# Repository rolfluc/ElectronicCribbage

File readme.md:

Repo Housing everything related to the electronic cribbage board project.
SW/ Contains everything for SW, including for test boards.
EE/ Contains all electrical aspects
HW/ Contains all HW related aspects

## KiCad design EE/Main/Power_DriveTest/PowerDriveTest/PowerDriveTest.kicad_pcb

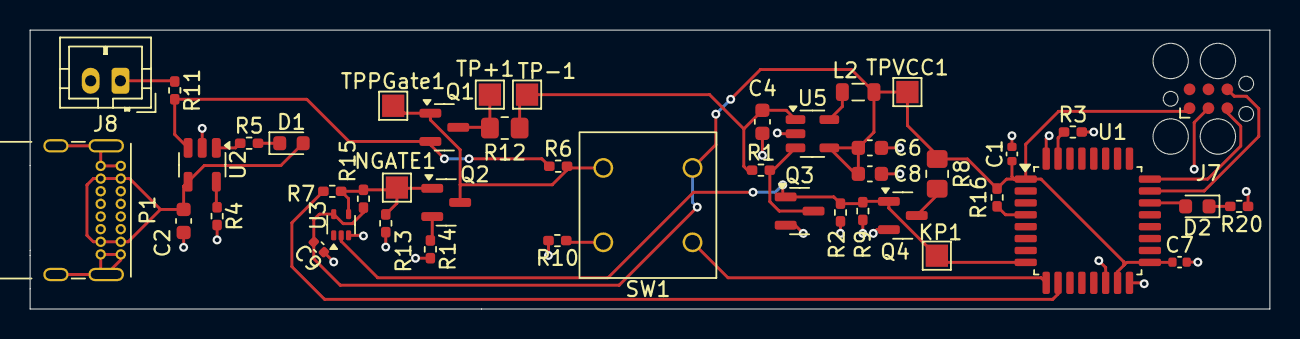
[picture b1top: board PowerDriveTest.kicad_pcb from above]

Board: 2 copper layers, 83.3 x 18.8 mm, 45 parts (0 on the bottom side), 26 nets.

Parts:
C1, C7, C9: 0.1u; C_0402_1005Metric
C2, C4, C6, C8: 4.7u; C_0603_1608Metric
D1, D2: LED; LED_0603_1608Metric
J7: TAG_CONNECT; Tag-Connect_TC2030-IDC-FP_2x03_P1.27mm_Vertical
J8: Conn_01x02_Male; JST_PH_B2B-PH-K_1x02_P2.00mm_Vertical
KP1: TestPoint; TestPoint_Pad_1.5x1.5mm
L2: 4.7u; L_0805_2012Metric
NGATE1: TestPoint; TestPoint_Pad_1.5x1.5mm
P1: USB_C_Plug_USB2.0; USB_C_Receptacle_GCT_USB4085
Q1: Q_PMOS_GSD; SOT-23
Q2, Q3, Q4: Q_NMOS_GSD; SOT-23
R1, R2, R9, R13: 100k; R_0402_1005Metric_Pad0.72x0.64mm_HandSolder
R3, R4, R10, R14, R16: 10k; R_0402_1005Metric_Pad0.72x0.64mm_HandSolder
R5, R20: 4.7k; R_0402_1005Metric_Pad0.72x0.64mm_HandSolder
R6: 1M; R_0402_1005Metric_Pad0.72x0.64mm_HandSolder
R7, R11: 0; R_0402_1005Metric_Pad0.72x0.64mm_HandSolder
R8: 10; R_0805_2012Metric_Pad1.20x1.40mm_HandSolder
R12: 25m; R_0805_2012Metric_Pad1.20x1.40mm_HandSolder
R15: 10K; R_0402_1005Metric_Pad0.72x0.64mm_HandSolder
SW1: SW_DPST; 401-1133-ND
TP+1: TestPoint; TestPoint_Pad_1.5x1.5mm
TP-1: TestPoint; TestPoint_Pad_1.5x1.5mm
TPPGate1: TestPoint; TestPoint_Pad_1.5x1.5mm
TPVCC1: TestPoint; TestPoint_Pad_1.5x1.5mm
U1: STM32G431K6Tx; LQFP-32_7x7mm_P0.8mm
U2: MCP73832-2-OT; SOT-23-5
U3: 74LVC1GU04DRL; SOT-553
U5: LM3670MF-3.3; TSOT-23-5

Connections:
+3V3: C1.1, C6.1, C7.1, C8.1, C9.1, J7.1 (POWER_3V3), L2.2, R8.1, R15.1, R16.1, SW1.1, TPVCC1.1, U1.1 (VDD), U1.15 (VDDA), U1.17 (VDD), U3.5 (VCC), U5.4 (FB)
/BTN_SNS: SW1.2, U1.9 (PA4)
/EN: Q3.3 (D), R1.2, U5.3 (EN)
/HB: D2.2 (A), U1.22 (PA12)
/KillPower: KP1.1, Q3.1 (G), Q4.1 (G), R2.1, R9.1, U1.8 (PA3), U3.2
/N_GATE: R7.1, U1.10 (PA5)
/N_SOURCE: Q2.2 (S), R14.1
/P_DRAIN: Q1.3 (D), R12.2, TP+1.1
/SWDCLK: J7.5 (SWCLK), U1.24 (PA14)
/SWDIO: J7.6 (SWDIO), U1.23 (PA13)
/VBAT: Q1.2 (S), R6.1, R11.2, U2.3 (VBAT)
/VBAT_OUT: C4.1, R1.1, R12.1, TP-1.1, U5.1 (Vin)
GND: C1.2, C2.2, C4.2, C6.2, C7.2, C8.2, C9.2, J7.3 (GND), J8.2, P1.A1 (GND), P1.A12 (GND), P1.B1 (GND), P1.B12 (GND), P1.S1 (SHIELD), Q3.2 (S), Q4.2 (S), R2.2, R3.2, R4.2, R9.2, R10.2, R13.2, R14.2, R20.1, U1.14 (VSSA), U1.16 (VSS), U1.32 (VSS), U2.2 (VSS), U3.3 (GND), U5.2 (GND)
unnamed: D1.1 (K), R5.2
unnamed: D2.1 (K), R20.2
unnamed: J8.1, R11.1
unnamed: Q1.1 (G), Q2.3 (D), R6.2, SW1.3, TPPGate1.1
unnamed: NGATE1.1, Q2.1 (G), R7.2, R13.1, R15.2, U3.4
unnamed: Q4.3 (D), R8.2
unnamed: R10.1, SW1.4
unnamed: R3.1, U1.31 (PB8)
unnamed: R16.2, U1.4 (PG10)
unnamed: R4.1, U2.5 (PROG)
unnamed: R5.1, U2.1 (STAT)
unnamed: L2.1, U5.5 (SW)
VBUS: C2.1, D1.2 (A), P1.A4 (VBUS), P1.A9 (VBUS), P1.B4 (VBUS), P1.B9 (VBUS), U2.4 (VDD)

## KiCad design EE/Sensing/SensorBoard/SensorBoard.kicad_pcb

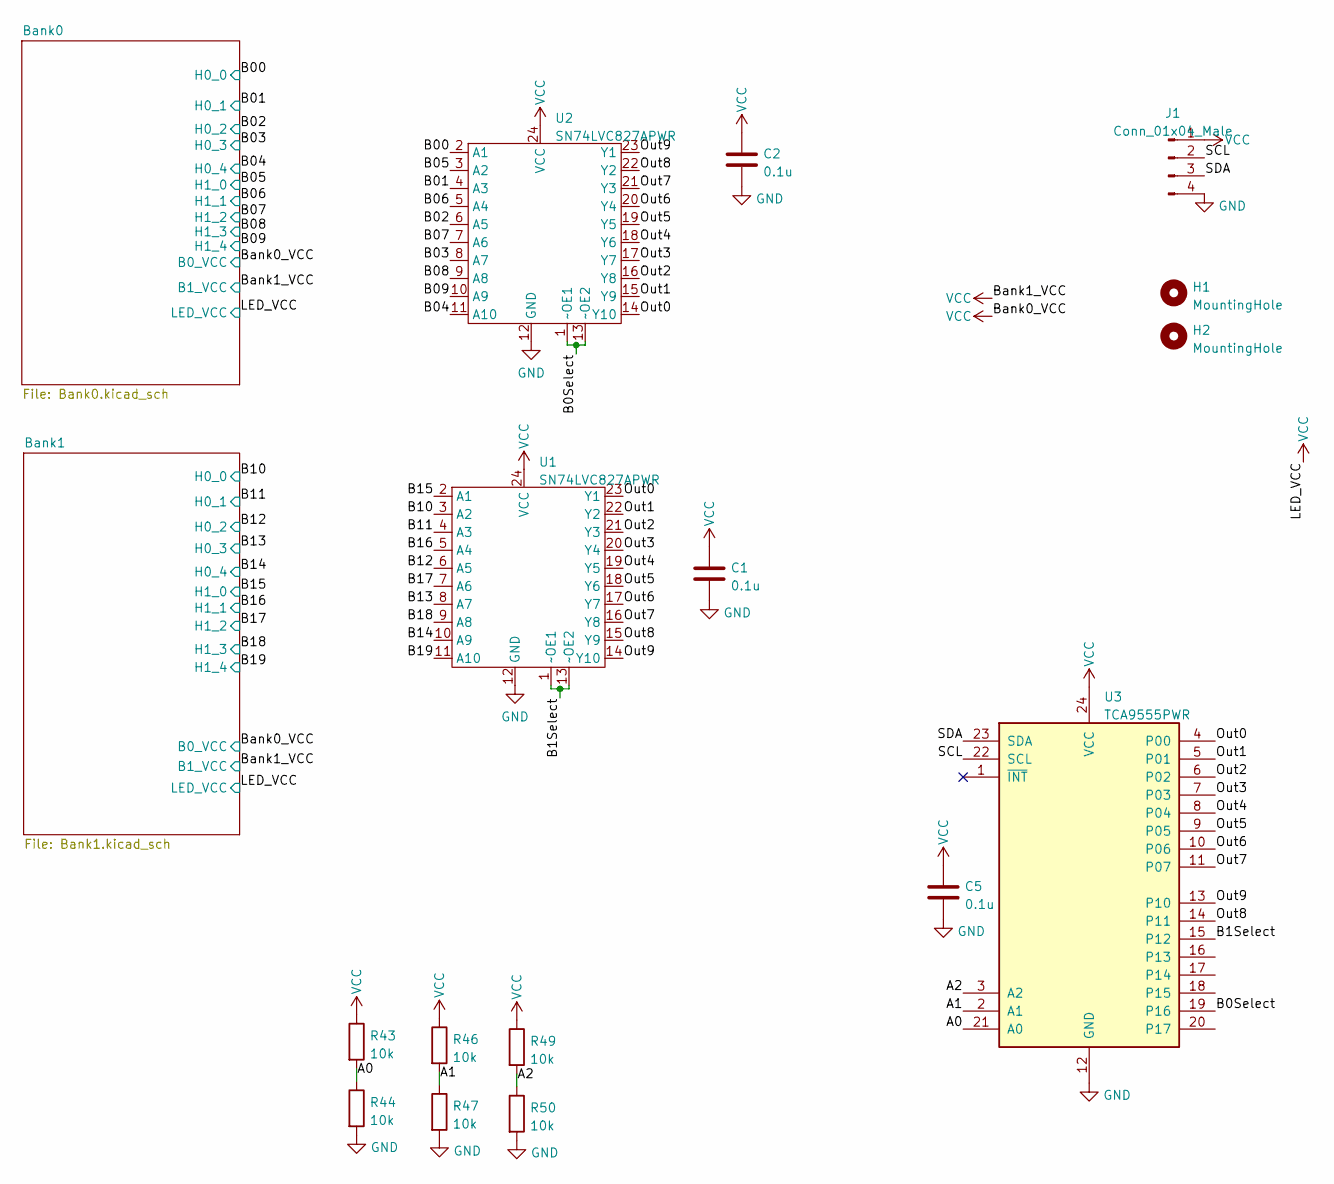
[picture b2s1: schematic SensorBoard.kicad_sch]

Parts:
C1, C2, C5: 0.1u; C_0402_1005Metric
H1, H2: MountingHole; MountingHole_2.5mm
J1: Conn_01x04_Male; PinSocket_1x04_P2.54mm_Vertical
R43, R44, R46, R47, R49, R50: 10k; R_0402_1005Metric
U1, U2: SN74LVC827APWR; TSSOP-24_4.4x7.8mm_P0.65mm
U3: TCA9555PWR; TSSOP-24_4.4x7.8mm_P0.65mm

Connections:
/A0: R43.2, R44.1, U3.21 (A0)
/A1: R46.2, R47.1, U3.2 (A1)
/A2: R49.2, R50.1, U3.3 (A2)
/B00: U2.2 (A1); also elsewhere on the board
/B0Select: U2.1 (~OE1), U2.13 (~OE2), U3.19 (P16)
/B01: U2.4 (A3); also elsewhere on the board
/B1Select: U1.1 (~OE1), U1.13 (~OE2), U3.15 (P12)
/B02: U2.6 (A5); also elsewhere on the board
/B03: U2.8 (A7); also elsewhere on the board
/B04: U2.11 (A10); also elsewhere on the board
/B05: U2.3 (A2); also elsewhere on the board
/B06: U2.5 (A4); also elsewhere on the board
/B07: U2.7 (A6); also elsewhere on the board
/B08: U2.9 (A8); also elsewhere on the board
/B09: U2.10 (A9); also elsewhere on the board
/B10: U1.3 (A2); also elsewhere on the board
/B11: U1.4 (A3); also elsewhere on the board
/B12: U1.6 (A5); also elsewhere on the board
/B13: U1.8 (A7); also elsewhere on the board
/B14: U1.10 (A9); also elsewhere on the board
/B15: U1.2 (A1); also elsewhere on the board
/B16: U1.5 (A4); also elsewhere on the board
/B17: U1.7 (A6); also elsewhere on the board
/B18: U1.9 (A8); also elsewhere on the board
/B19: U1.11 (A10); also elsewhere on the board
/Out0: U1.23 (Y1), U2.14 (Y10), U3.4 (P00)
/Out1: U1.22 (Y2), U2.15 (Y9), U3.5 (P01)
/Out2: U1.21 (Y3), U2.16 (Y8), U3.6 (P02)
/Out3: U1.20 (Y4), U2.17 (Y7), U3.7 (P03)
/Out4: U1.19 (Y5), U2.18 (Y6), U3.8 (P04)
/Out5: U1.18 (Y6), U2.19 (Y5), U3.9 (P05)
/Out6: U1.17 (Y7), U2.20 (Y4), U3.10 (P06)
/Out7: U1.16 (Y8), U2.21 (Y3), U3.11 (P07)
/Out8: U1.15 (Y9), U2.22 (Y2), U3.14 (P11)
/Out9: U1.14 (Y10), U2.23 (Y1), U3.13 (P10)
/SCL: J1.2, U3.22 (SCL)
/SDA: J1.3, U3.23 (SDA)
GND: C1.2, C2.2, C5.2, J1.4, R44.2, R47.2, R50.2, U1.12 (GND), U2.12 (GND), U3.12 (GND); also elsewhere on the board
VCC: C1.1, C2.1, C5.1, J1.1, R43.1, R46.1, R49.1, U1.24 (VCC), U2.24 (VCC), U3.24 (VCC); also elsewhere on the board

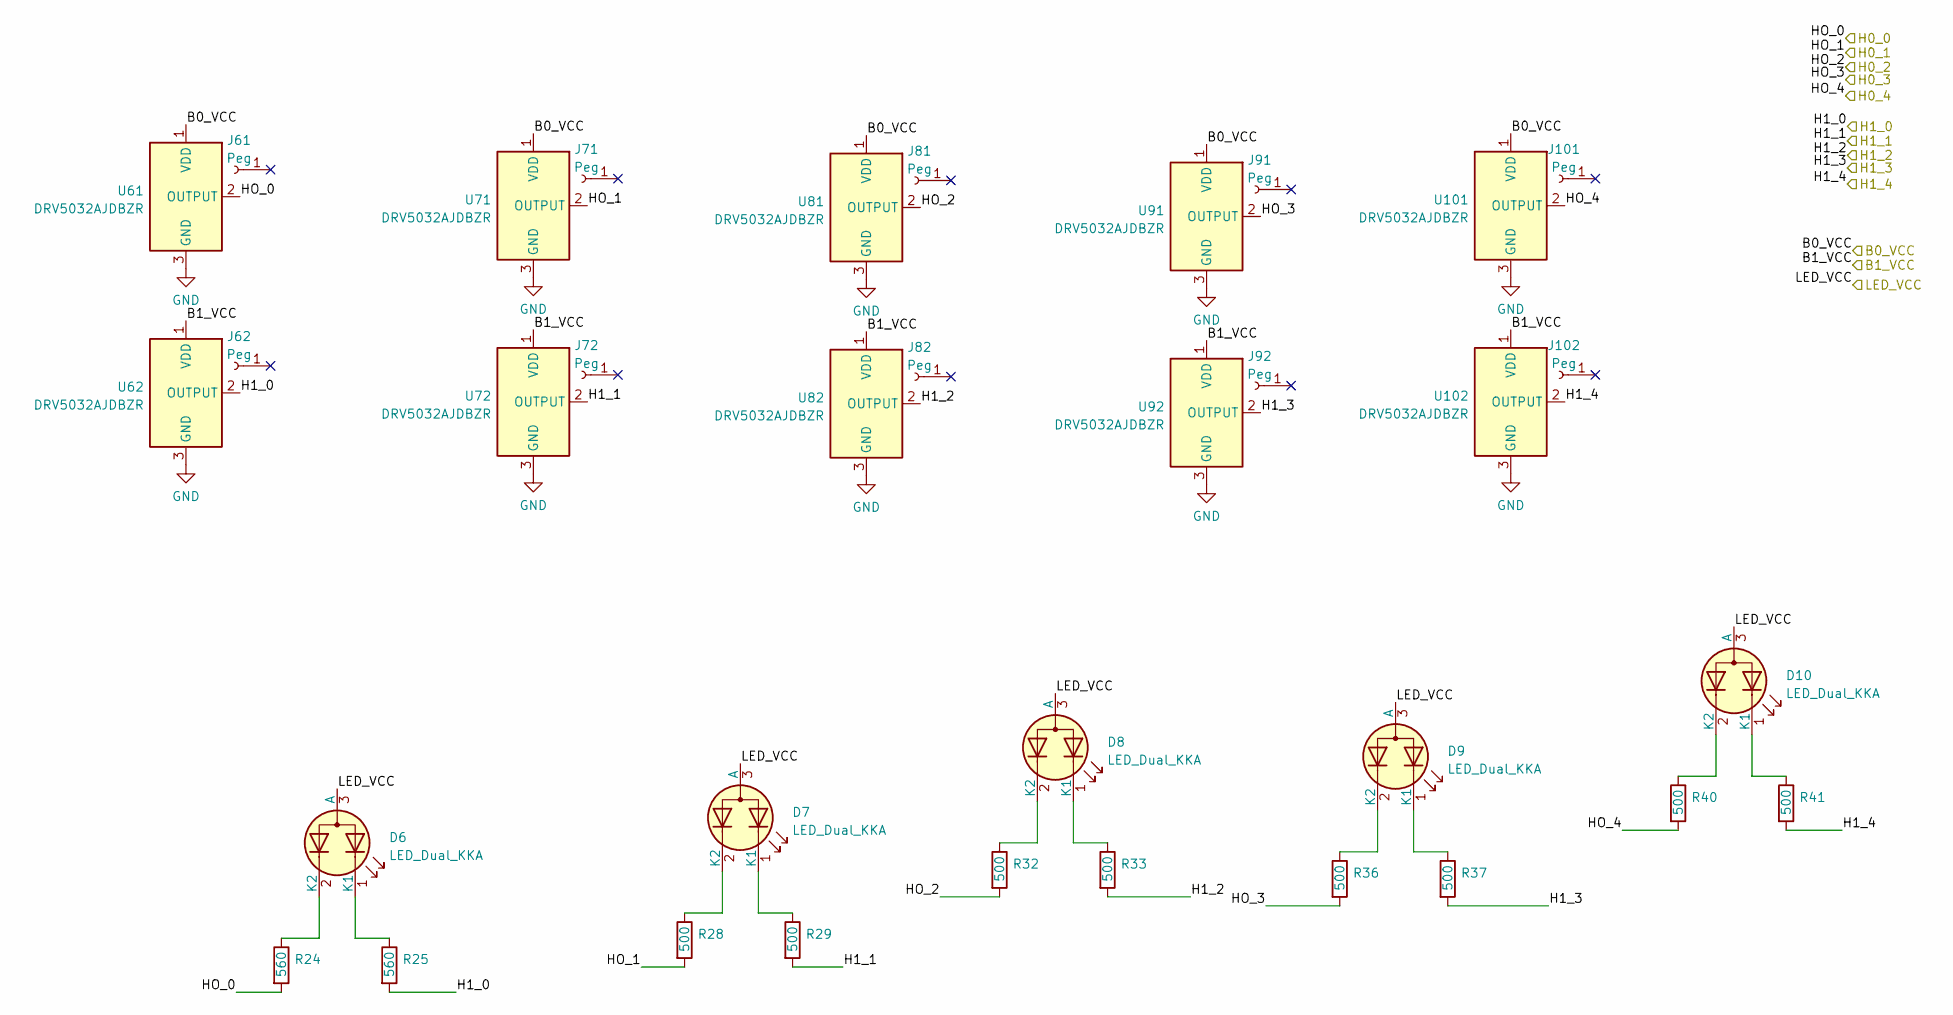
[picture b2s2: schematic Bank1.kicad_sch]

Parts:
D6, D7, D8, D9, D10: LED_Dual_KKA; SOT-23
J61, J62, J71, J72, J81, J82, J91, J92, J101, J102: Peg; TestPattern0
R24, R25: 560; R_0402_1005Metric_Pad0.72x0.64mm_HandSolder
R28, R29, R32, R33, R36, R37, R40, R41: 500; R_0402_1005Metric_Pad0.72x0.64mm_HandSolder
U61, U62, U71, U72, U81, U82, U91, U92, U101, U102: DRV5032AJDBZR; SOT-23

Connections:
/B10: R24.2, U61.2 (OUTPUT); also elsewhere on the board
/B11: R28.2, U71.2 (OUTPUT); also elsewhere on the board
/B12: R32.2, U81.2 (OUTPUT); also elsewhere on the board
/B13: R36.2, U91.2 (OUTPUT); also elsewhere on the board
/B14: R40.2, U101.2 (OUTPUT); also elsewhere on the board
/B15: R25.2, U62.2 (OUTPUT); also elsewhere on the board
/B16: R29.2, U72.2 (OUTPUT); also elsewhere on the board
/B17: R33.2, U82.2 (OUTPUT); also elsewhere on the board
/B18: R37.2, U92.2 (OUTPUT); also elsewhere on the board
/B19: R41.2, U102.2 (OUTPUT); also elsewhere on the board
GND: U61.3 (GND), U62.3 (GND), U71.3 (GND), U72.3 (GND), U81.3 (GND), U82.3 (GND), U91.3 (GND), U92.3 (GND), U101.3 (GND), U102.3 (GND); also elsewhere on the board
unnamed: D6.1 (K1), R25.1
unnamed: D6.2 (K2), R24.1
unnamed: D7.1 (K1), R29.1
unnamed: D7.2 (K2), R28.1
unnamed: D8.1 (K1), R33.1
unnamed: D8.2 (K2), R32.1
unnamed: D9.1 (K1), R37.1
unnamed: D9.2 (K2), R36.1
unnamed: D10.1 (K1), R41.1
unnamed: D10.2 (K2), R40.1
VCC: D6.3 (A), D7.3 (A), D8.3 (A), D9.3 (A), D10.3 (A), U61.1 (VDD), U62.1 (VDD), U71.1 (VDD), U72.1 (VDD), U81.1 (VDD), U82.1 (VDD), U91.1 (VDD), U92.1 (VDD), U101.1 (VDD), U102.1 (VDD); also elsewhere on the board

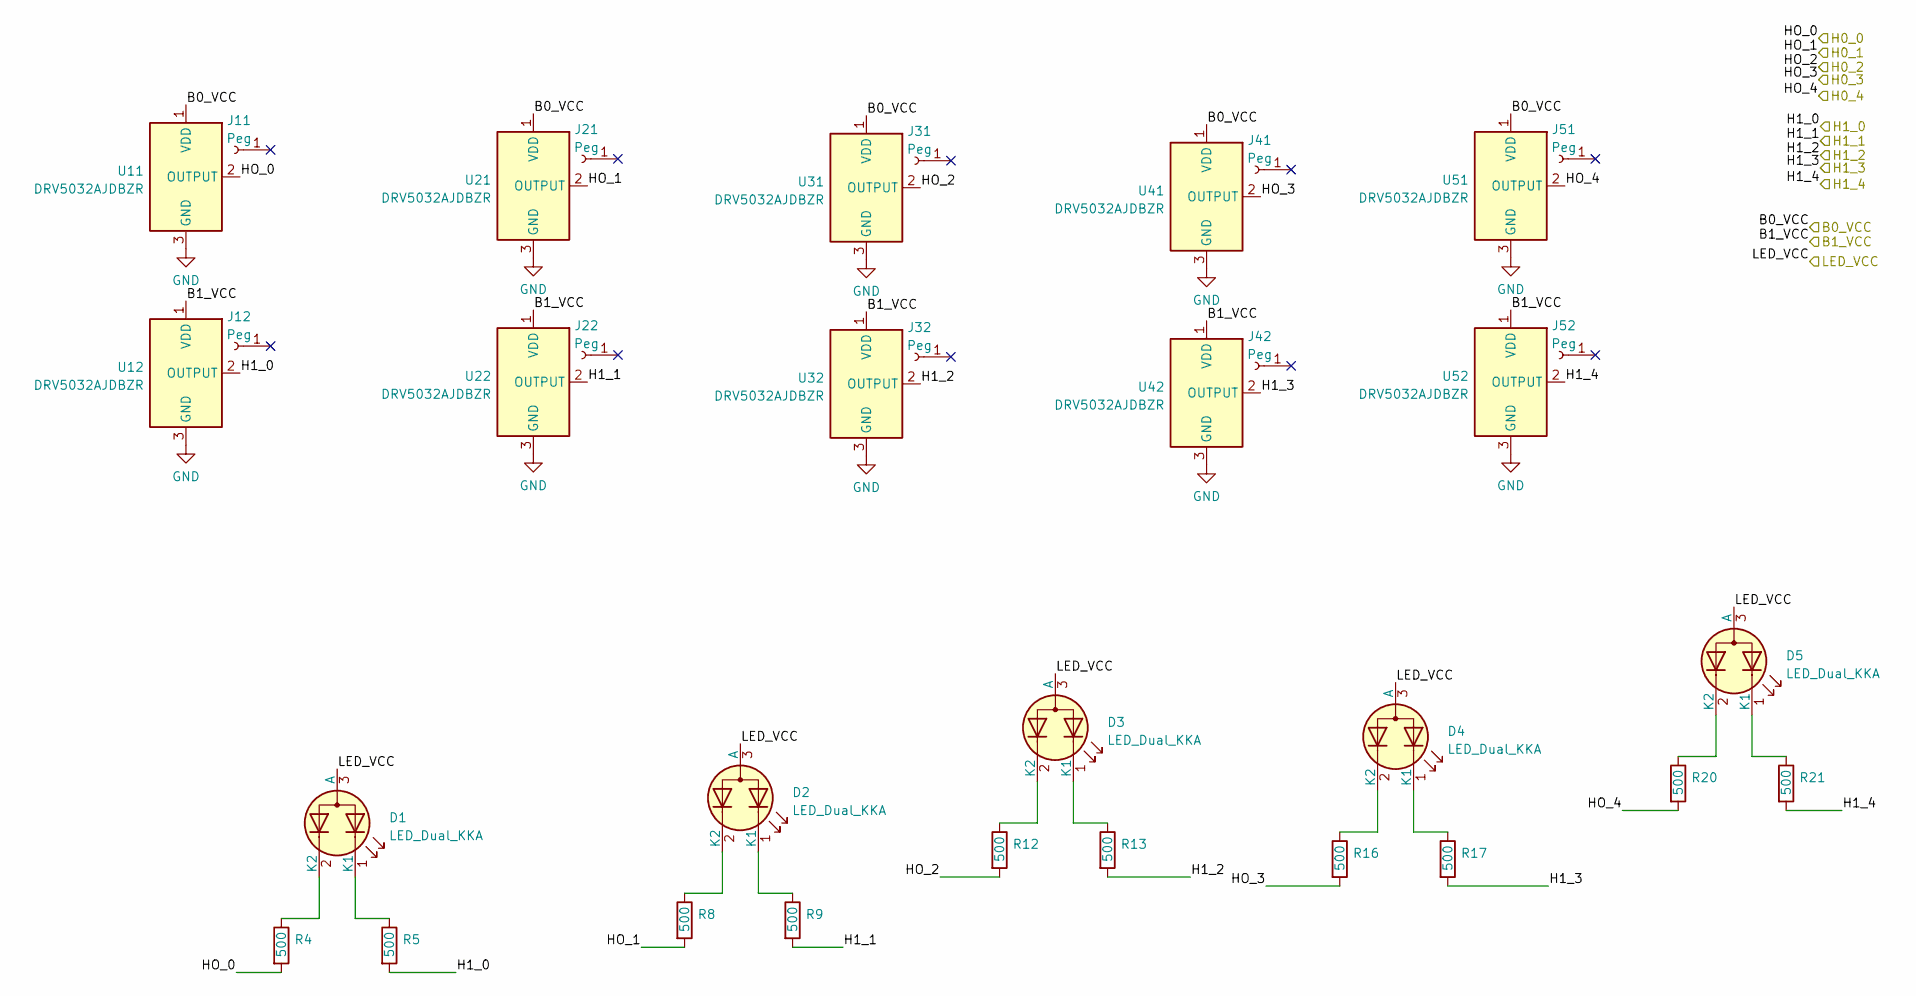
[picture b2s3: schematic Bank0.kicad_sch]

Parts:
D1, D2, D3, D4, D5: LED_Dual_KKA; SOT-23
J11, J12, J21, J22, J31, J32, J41, J42, J51, J52: Peg; TestPattern0
R4, R5, R8, R9, R12, R13, R16, R17, R20, R21: 500; R_0402_1005Metric_Pad0.72x0.64mm_HandSolder
U11, U12, U21, U22, U31, U32, U41, U42, U51, U52: DRV5032AJDBZR; SOT-23

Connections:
/B00: R4.2, U11.2 (OUTPUT); also elsewhere on the board
/B01: R8.2, U21.2 (OUTPUT); also elsewhere on the board
/B02: R12.2, U31.2 (OUTPUT); also elsewhere on the board
/B03: R16.2, U41.2 (OUTPUT); also elsewhere on the board
/B04: R20.2, U51.2 (OUTPUT); also elsewhere on the board
/B05: R5.2, U12.2 (OUTPUT); also elsewhere on the board
/B06: R9.2, U22.2 (OUTPUT); also elsewhere on the board
/B07: R13.2, U32.2 (OUTPUT); also elsewhere on the board
/B08: R17.2, U42.2 (OUTPUT); also elsewhere on the board
/B09: R21.2, U52.2 (OUTPUT); also elsewhere on the board
GND: U11.3 (GND), U12.3 (GND), U21.3 (GND), U22.3 (GND), U31.3 (GND), U32.3 (GND), U41.3 (GND), U42.3 (GND), U51.3 (GND), U52.3 (GND); also elsewhere on the board
unnamed: D1.1 (K1), R5.1
unnamed: D1.2 (K2), R4.1
unnamed: D2.1 (K1), R9.1
unnamed: D2.2 (K2), R8.1
unnamed: D3.1 (K1), R13.1
unnamed: D3.2 (K2), R12.1
unnamed: D4.1 (K1), R17.1
unnamed: D4.2 (K2), R16.1
unnamed: D5.1 (K1), R21.1
unnamed: D5.2 (K2), R20.1
VCC: D1.3 (A), D2.3 (A), D3.3 (A), D4.3 (A), D5.3 (A), U11.1 (VDD), U12.1 (VDD), U21.1 (VDD), U22.1 (VDD), U31.1 (VDD), U32.1 (VDD), U41.1 (VDD), U42.1 (VDD), U51.1 (VDD), U52.1 (VDD); also elsewhere on the board

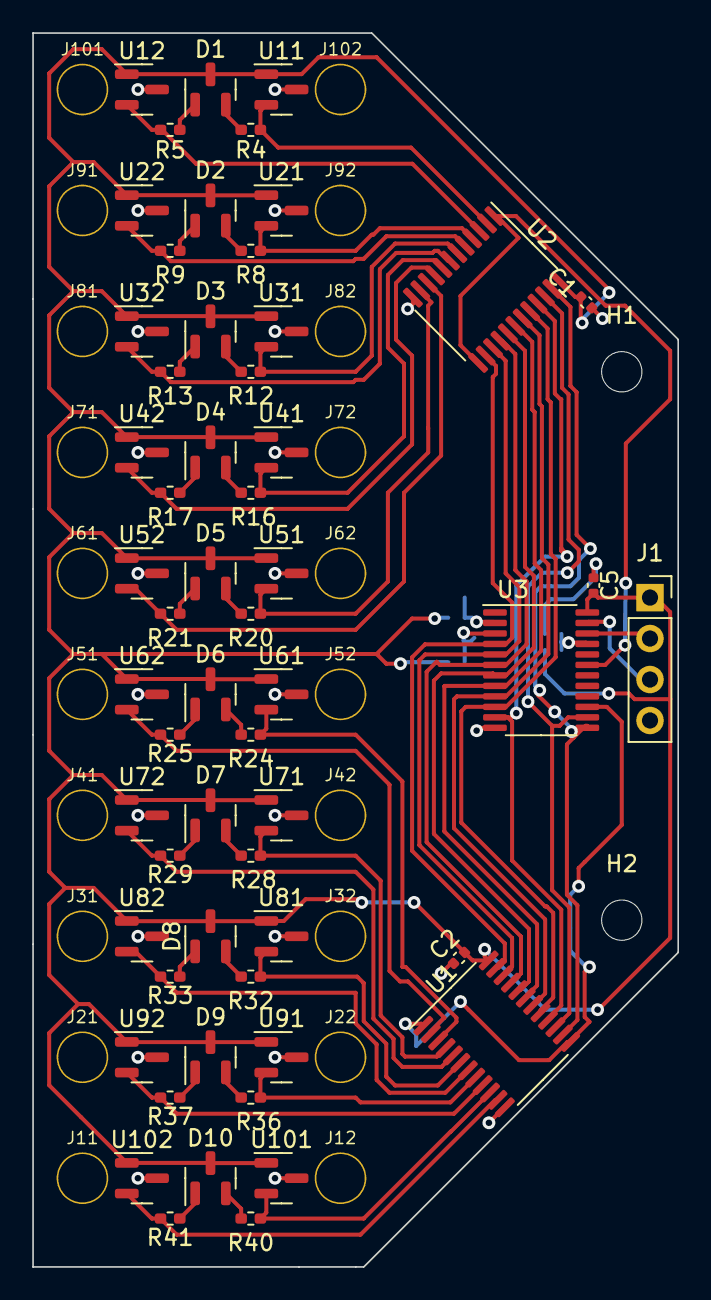
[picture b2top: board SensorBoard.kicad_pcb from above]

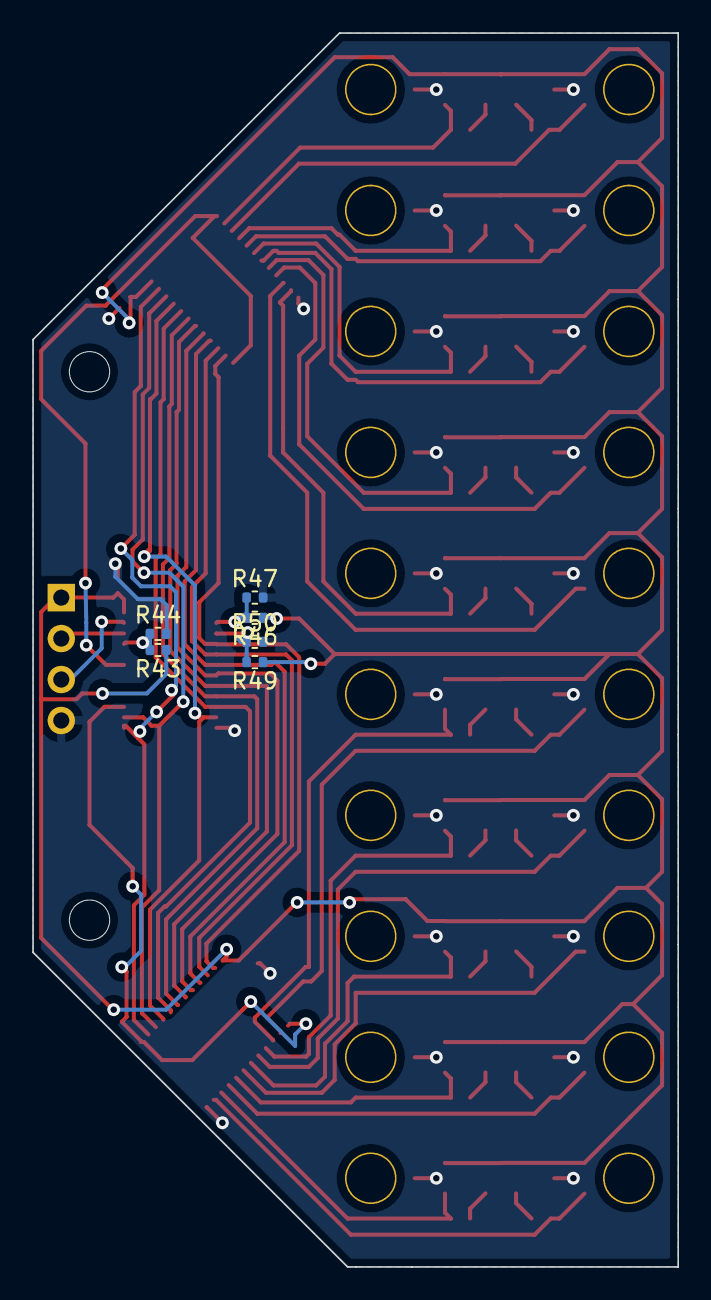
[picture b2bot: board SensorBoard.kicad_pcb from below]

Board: 2 copper layers, 40.0 x 76.5 mm, 85 parts (6 on the bottom side), 59 nets.

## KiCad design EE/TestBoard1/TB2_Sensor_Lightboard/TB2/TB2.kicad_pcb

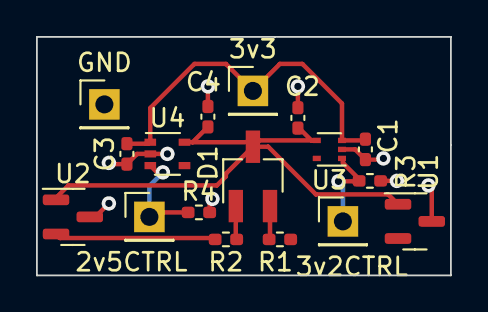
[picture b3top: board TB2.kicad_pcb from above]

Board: 2 copper layers, 23.0 x 13.2 mm, 17 parts (0 on the bottom side), 9 nets.

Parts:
2v5CTRL, 3v2CTRL, 3v3: Conn_01x01_Female; PinHeader_1x01_P2.54mm_Vertical
C1, C2, C3, C4: 0.1u; C_0402_1005Metric_Pad0.74x0.62mm_HandSolder
D1: LED_Dual_KKA; SC-59_Handsoldering
GND: Conn_01x01_Female; PinHeader_1x01_P2.54mm_Vertical
R1, R2: 1k; R_0402_1005Metric_Pad0.72x0.64mm_HandSolder
R3, R4: 100k; R_0402_1005Metric_Pad0.72x0.64mm_HandSolder
U1, U2: AH1381; SOT-23
U3: TCR2EE32; SOT-553
U4: MIC5365-2.5YC5; SOT-353_SC-70-5

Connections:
+3V3: 3v3.1, C1.1, C3.1, U3.3 (VIN), U4.1 (VIN)
/2v5_CTRL: 2v5CTRL.1, R4.1, U4.3 (EN)
/3v2_CTRL: 3v2CTRL.1, R3.1, U3.1 (CTRL)
/HO_0: R1.2, U1.2 (OUTPUT)
/HO_1: R2.2, U2.2 (OUTPUT)
GND: C1.2, C2.2, C3.2, C4.2, GND.1, R3.2, R4.2, U1.3 (GND), U2.3 (GND), U3.2 (GND), U4.2 (GND)
unnamed: D1.1 (K1), R2.1
unnamed: D1.2 (K2), R1.1
VCC: C2.1, C4.1, D1.3 (A), U1.1 (VDD), U2.1 (VDD), U3.4 (VOUT), U4.5 (VOUT)

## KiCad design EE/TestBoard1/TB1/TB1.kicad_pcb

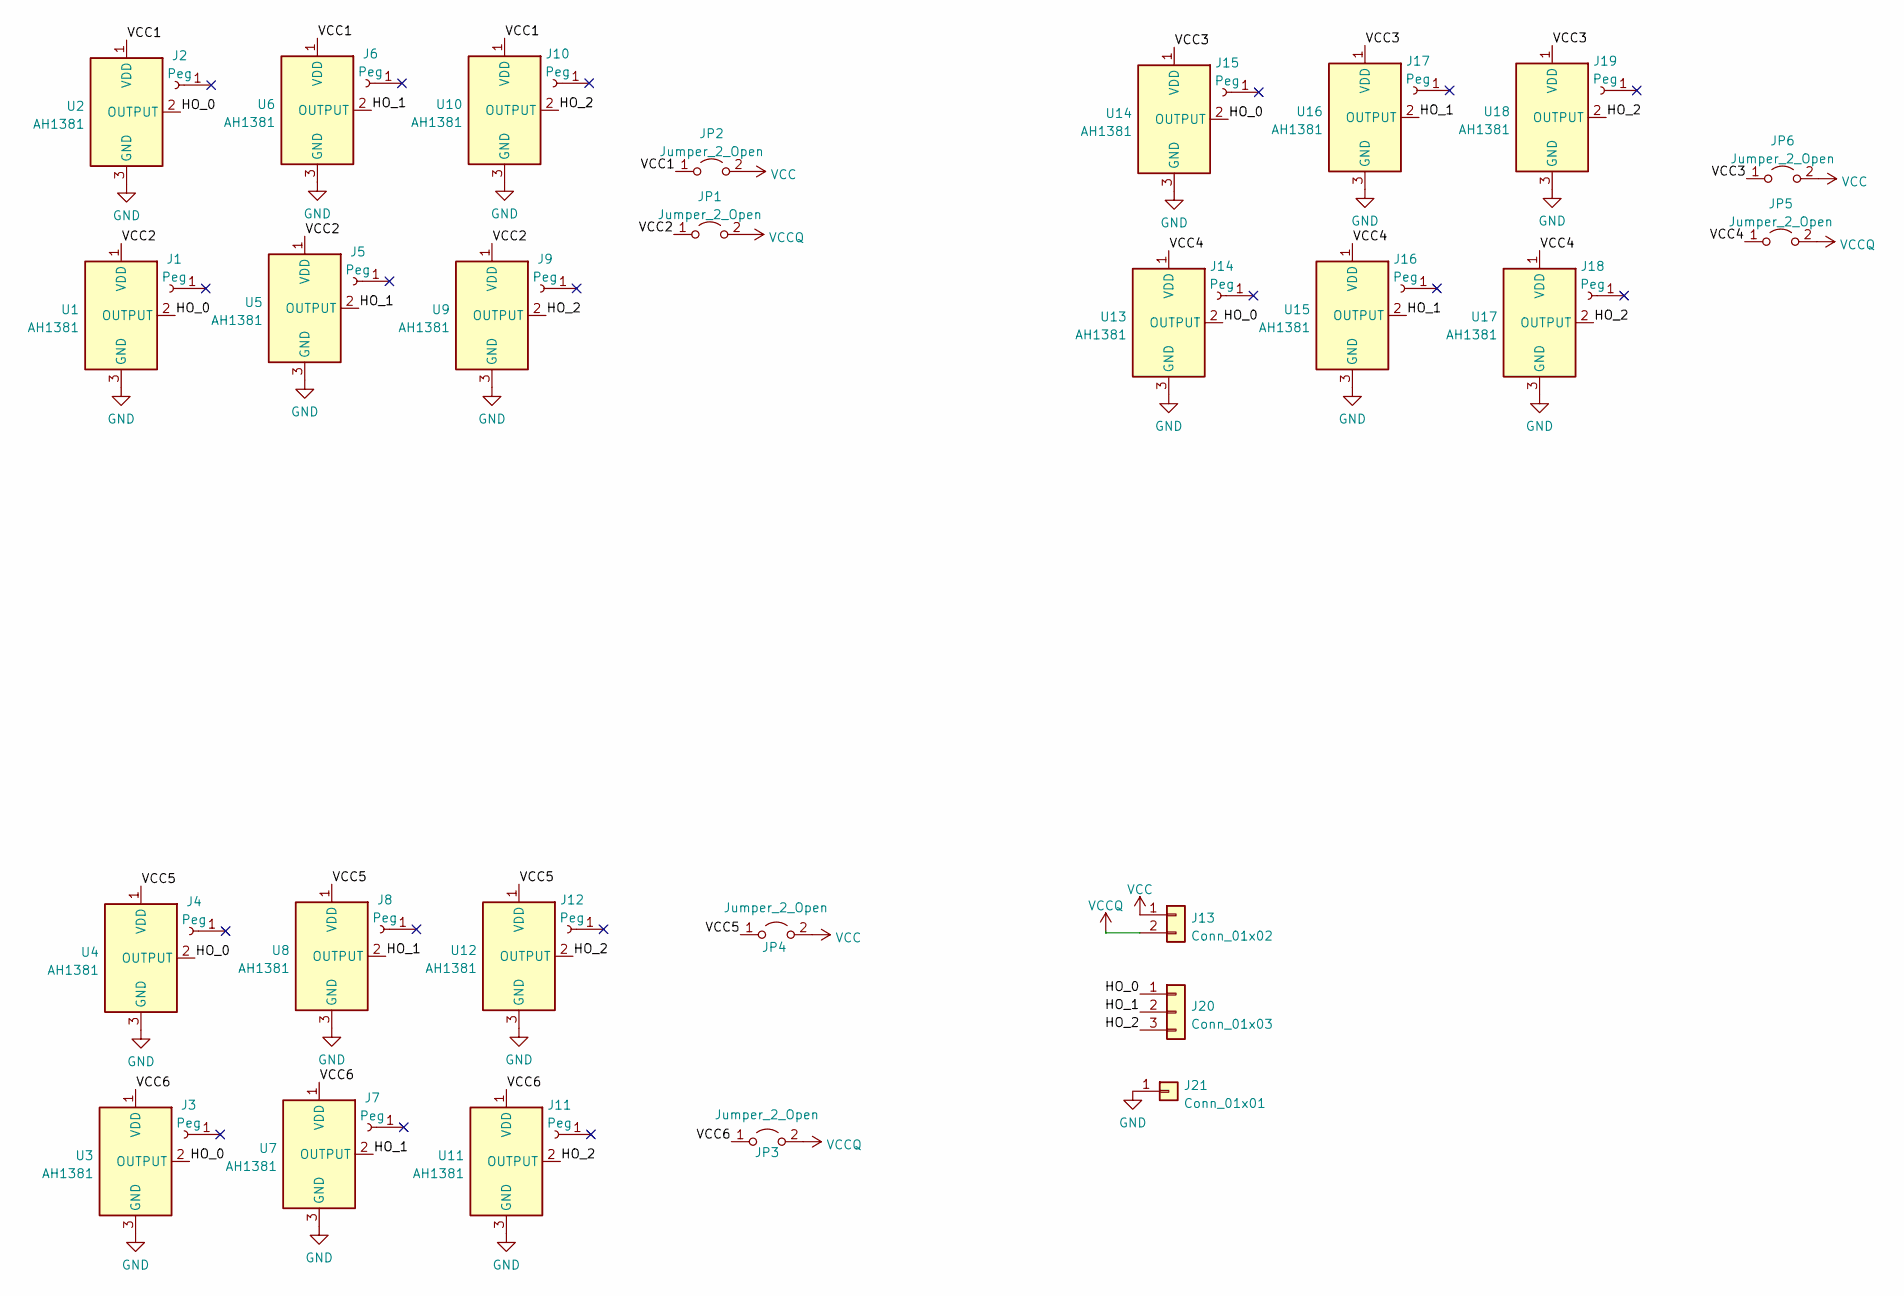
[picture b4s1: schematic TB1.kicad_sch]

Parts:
J1, J2, J5, J6, J9, J10: Peg; TestPattern0
J3, J4, J7, J8, J11, J12: Peg; TestPattern1
J13: Conn_01x02; PinHeader_1x02_P2.54mm_Vertical
J14, J15, J16, J17, J18, J19: Peg; TestPattern2
J20: Conn_01x03; PinHeader_1x03_P2.54mm_Vertical
J21: Conn_01x01; PinHeader_1x01_P2.54mm_Vertical
JP1, JP2, JP3, JP4, JP5, JP6: Jumper_2_Open; SolderJumper-2_P1.3mm_Open_Pad1.0x1.5mm
U1, U2, U3, U4, U5, U6, U7, U8, U9, U10, U11, U12, U13, U14, U15, U16, U17, U18: AH1381; SOT-23

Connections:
/HO_0: J20.1, U1.2 (OUTPUT), U2.2 (OUTPUT), U3.2 (OUTPUT), U4.2 (OUTPUT), U13.2 (OUTPUT), U14.2 (OUTPUT)
/HO_1: J20.2, U5.2 (OUTPUT), U6.2 (OUTPUT), U7.2 (OUTPUT), U8.2 (OUTPUT), U15.2 (OUTPUT), U16.2 (OUTPUT)
/HO_2: J20.3, U9.2 (OUTPUT), U10.2 (OUTPUT), U11.2 (OUTPUT), U12.2 (OUTPUT), U17.2 (OUTPUT), U18.2 (OUTPUT)
/VCC1: JP2.1 (A), U2.1 (VDD), U6.1 (VDD), U10.1 (VDD)
/VCC2: JP1.1 (A), U1.1 (VDD), U5.1 (VDD), U9.1 (VDD)
/VCC3: JP6.1 (A), U14.1 (VDD), U16.1 (VDD), U18.1 (VDD)
/VCC4: JP5.1 (A), U13.1 (VDD), U15.1 (VDD), U17.1 (VDD)
/VCC5: JP4.1 (A), U4.1 (VDD), U8.1 (VDD), U12.1 (VDD)
/VCC6: JP3.1 (A), U3.1 (VDD), U7.1 (VDD), U11.1 (VDD)
GND: J21.1, U1.3 (GND), U2.3 (GND), U3.3 (GND), U4.3 (GND), U5.3 (GND), U6.3 (GND), U7.3 (GND), U8.3 (GND), U9.3 (GND), U10.3 (GND), U11.3 (GND), U12.3 (GND), U13.3 (GND), U14.3 (GND), U15.3 (GND), U16.3 (GND), U17.3 (GND), U18.3 (GND)
VCC: J13.1, JP2.2 (B), JP4.2 (B), JP6.2 (B)
VCCQ: J13.2, JP1.2 (B), JP3.2 (B), JP5.2 (B)

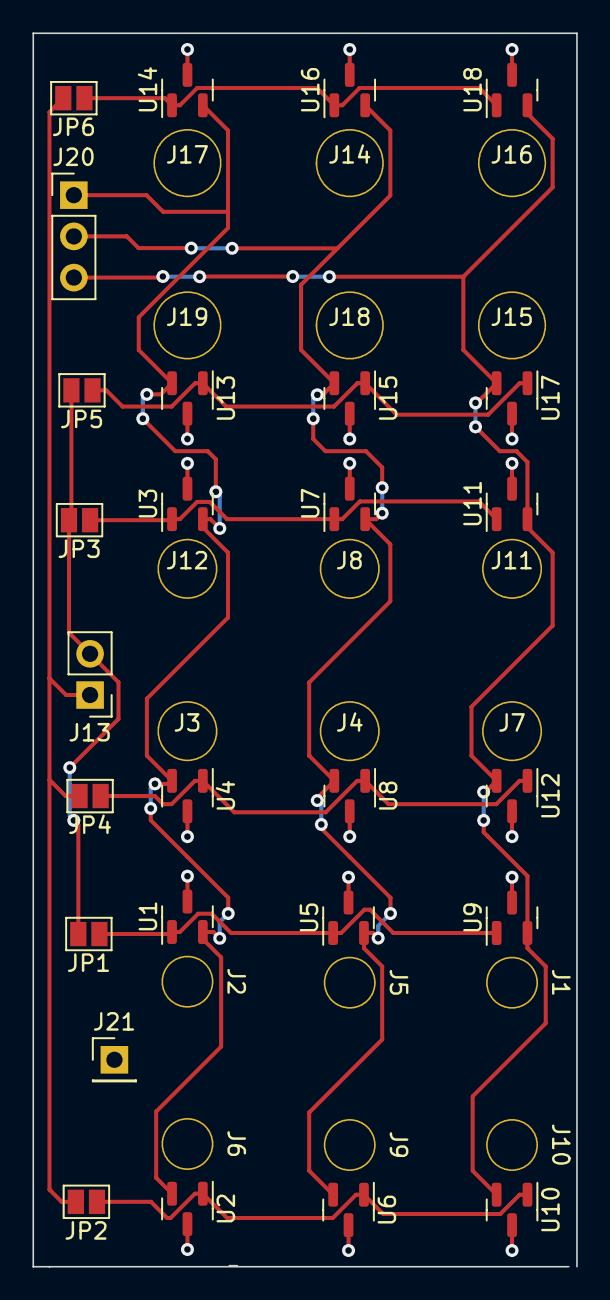
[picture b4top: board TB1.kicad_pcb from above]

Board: 2 copper layers, 33.5 x 76.0 mm, 45 parts (0 on the bottom side), 12 nets.

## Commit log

2024-02-06 First commit - Readme & Project Layout
2024-02-06 Schematic For Test Board 1, Layout Start
2024-02-06 Finished TB1 for Magnet Test
2024-02-19 Adding Lighting Test Board - ordered
2024-02-19 Adding Bank Sensor for 6x10 design idea
2024-03-01 WIP - TBs ordered, Sensor board pre layout sensor board
2024-03-01 First pass layout of LEDs/ Sensors
2024-03-01 More Layout
2024-03-01 All on top layer
2024-03-01 Front Layout, Smaller silkscreen
2024-03-01 Sensors attached to mainboard
2024-03-02 New Layout - Better Sensorboard
2024-03-04 Mainboard Layout Setup
2024-03-04 First pass exterior
2024-03-23 WIP - Moving Sensor to IO Expander
2024-03-23 Fix of Multiplexing
2024-03-23 Fixing Routing
2024-03-23 Fixed Routing
2024-03-23 Fixed Silkscreens
2024-03-24 Updated layout, and placement for main board
2024-03-24 Routed PCB, Need SCL/SDA still
2024-03-24 First pass Finalized Layout. Pending Sensing board changes.
2024-03-25 Pre Order for Sensor Board
2024-04-01 SW Start
2024-04-03 WIP - Small checkin
2024-04-04 Display Controller Enabled
    Enabling Controller. Need Further Integration.
2024-04-04 Peg Handler Start
2024-05-11 WIP - Working on Peg Logic
2024-05-12 Display Theoretically working
    Display changed to show left or right on timer change.
2024-05-12 Modified Setting Display Vals
2024-05-12 WIP - Pin and Point Handling
2024-05-13 Integrating Pegs, and Display Names
2024-05-23 Replacement after sensing change
2024-05-23 Potential Layout - Inverted 1 chip for layout
2024-05-24 Shipped new boards
2024-10-02 Routine Update
2024-10-20 Random Check in
2024-10-21 Sample Board for Power Supplies, Micro, And LED Driving.
2024-10-24 First pass layout
    Assumes using Cut-through RGB 7 Segment
2024-10-24 Adding Ground Stitches
2024-11-17 New Power Board off to mfging
2024-11-17 MCU Modification
    Migrated to g431, as is used elsewhere.
2024-12-24 Routine Checkout
2025-01-02 Potential Layout. Need to confirm button and L&F.
2025-02-03 Potential Revision
    Potentially fabb-able rev.
2025-03-13 Checkin of Fabbed Board
2025-04-06 PinDef Assigned, Power Handler Started, to ensure power remains on after boot
2025-04-06 Added some logic for Peg Handling.
2025-04-06 Removing PWM References
2025-04-06 Started HB, Migrated SPI control of LEDs
2025-04-06 Display Control Scheme Change, ADC Added but incomplete
2025-04-07 Adding LV Detection
2025-04-08 WIP state machine handler for Pegs
2025-04-28 Positioning for Boards
2025-04-28 WIP case. Added supports for pegs.
2025-04-28 Base Exterior Case
2025-04-30 WIP case top
2025-07-25 Starting Sim for Cribbage
2025-07-26 Drawing Hexagon
2025-07-26 Colors changing on press.
2025-07-26 Limited to 2 Pegs
2025-07-27 Working Difference calc
2025-07-27 Overflow calc
2025-07-29 Printed Case
2025-07-29 Updated EE
2025-08-02 Untested Display State Machine
    In theory, Display should be close to working for scrolling text.
    Has a User vs System display, as User can request battery voltage.
2025-08-02 WIP on peg Handler State Machine
2025-08-03 Fixed Build
2025-08-03 Working Display State Machine, Not Working Peg Reader
2025-08-09 Cleanup, and Working 1 Bank Reading
2025-08-09 Each Peg Works
2025-08-09 Better Text for Go
2025-08-09 Working On Board Pegs
2025-08-11 First Peg Numeric Working, and R/G Detection
2025-08-14 WIP - Working towards multi peg handling
2025-08-15 First pass State machine for startup. Not fully functional.
2025-08-15 Possibly working peg state machine. Needs testing
2025-08-18 Updated Corner cases for the state machine handler
2025-08-18 Updating Format, Adding Rev2 Start
2025-08-18 Schematic Change, Attempting new power circuit to turn off, with MCU
2025-08-19 Placement Update
2025-08-19 Slightly better init condition handling
2025-08-20 Better working Timing / Switching for early state machine
2025-08-23 Delta appears to be working correctly.
2025-08-23 Enabling Button Hold to Reset Game
2025-08-23 Fixed Blinking Issue with incorrect Timing, Peg Handling
2025-08-23 Increasing Brightness, Updating naming
2025-08-24 Adding Pegs to version control
2025-08-24 Adding holes to contain the pegs
    Still need mounting brackets.
2025-08-25 Printed Model
2025-08-26 Added Insert for Peg holes for storage
2025-08-26 Functioning ADC
2025-08-27 Working Voltage Reading
2025-08-29 Adding Test Circuit 2
